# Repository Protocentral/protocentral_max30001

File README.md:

# ProtoCentral MAX30001 ECG and Respiration/Bio-Impedance Breakout Board

If you dont already have one, you can buy [ProtoCentral MAX30001 ECG and Respiration/Bio-Impedance Breakout Board here.](https://protocentral.com/product/protocentral-max30001/)

MAX30001 is a single-lead ECG monitoring IC which has built-in R-R detection and several other features that make it perfect for a wearable single-lead ECG application.  

Several new features on this chip make it ideal for wearable applications. First is the low power consumption - just 85 uW of power and can work from 1.1 V onwards ! Also of interest is the fact that it can work with only two chest electrodes without the need for a third right-leg drive (DRL) electrode.

The best feature of this chip though is the built-in R-R detection algorithm which can measure the time between successive peaks of the QRS complex of the ECG. This means that heart-computation comes right out of the box without any microcontroller-side code requirement. Heart-rate computation just got a lot easier !!

# Features

* MAX30001 single channel integrated front-end (AFE) chip
* Single-lead ECG monitoring ( three electrodes, optional right leg drive)
* Capable of measuring respiration
* Clinical-Grade ECG and BioZ AFE with High Resolution
* Inbuilt R-R detection and Pace detection
* Flexibility for 2 or 3 electrode measurements
* ADC Resolution is 18 bits 
* High DC Offset range of ±650mV(excellent tolerance to motion artifacts)
* Onboard 3.3V voltage regulator for low noise.
* Onboard logic level translators for Arduino interface.

# What's included

* ProtoCentral MAX30001 ECG and Respiration/Bio-Impedance Breakout Board
* Straight pin headers
* 2-electrode ECG connector with stereo connector
* 10x disposable ECG stick-on electrodes

# Repository Contents

* **/software** - Arduino library and example sketches.
* **/hardware** - All Eagle hardware design files

# Wiring the board to your Arduino

If you have bought the breakout the connection with the Arduino board is as follows:

|MAX30001 pin label| Arduino Connection   |Pin Function      |
|----------------- |:--------------------:|-----------------:|
| MISO             | D12                  |  Slave out|             
| MOSI             | D11                  |  Slave in           |
| SCK              | D13                  |  Serial clock     |
| CS0              | D7                   |  Slave select|
| FCLK             | NC                   |  External clock(32KHz)     |
| INT1             | D2                   |  Interrupt        |
| INT2             | NC                   |  Interrupt       |
| 3V3              | Supply               |  Board which supports 3.3V and 1.8V    |
| VCC              | Supply 5V            | 5V            |
| GND              | Gnd  

# Running the Arduino Sketch

If you have correctly installed the libraries, the example sketeches should now be available from within Arduino.

[Download the Arduino Sketch here for this board here.](https://github.com/Protocentral/protocentral_max30001/releases/download/v0.1/protocentral_max30001_arduino.zip)

Open up your Arduino IDE and run the Arudino sketch (.ino) file in the archive that you downloaded. Your Arduino should now be programmed to read the ecg data and sending over the USB-UART.  

# Using the ProtoCentral OpenView GUI

The GUI for visualizing the ECG and Respiration as well as parameters like Heart rate and Respiration rate is written in Processing, based on Java and is cross-compilable across platforms.

Java 8 is required on all platforms for running the processing-based GUI application. You can download Java for your platform from the [Official Java website](https://www.java.com/en/download/).

You can download and install [ProtoCentral OpenView from here](https://github.com/Protocentral/protocentral_openview).

Once you have opened OpenView, make sure to select "MAX30001 breakout" under the "Board" dropdown. 

# Connecting the ECG Electrodes

A 2-electrode cable along with a standard stereo jack is provided along with the shield to connect the electrodes to the board. The electrode input connector is highlighted in the below picture.

The other side of the electrode connector would connect to snap-on electrodes attached to the body. For testing purposes, you can use an ECG simulator to provide inputs to the board.

*Warning:
When connecting the electodes to the body, it is safer to disconnect the mains power source to the Arduino. For example, if  you are using the Arduino along with a laptop, disconnecting the battery charger from the laptop would be a safe option.*

# Placing the Electrodes on the body

License Information
===================

This product is open source! Both, our hardware and software are open source and licensed under the following licenses:

Hardware
---------

**All hardware is released under the [CERN-OHL-P v2](https://ohwr.org/cern_ohl_p_v2.txt)** license.

Copyright CERN 2020.

This source describes Open Hardware and is licensed under the CERN-OHL-P v2.

You may redistribute and modify this documentation and make products
using it under the terms of the CERN-OHL-P v2 (https:/cern.ch/cern-ohl).
This documentation is distributed WITHOUT ANY EXPRESS OR IMPLIED
WARRANTY, INCLUDING OF MERCHANTABILITY, SATISFACTORY QUALITY
AND FITNESS FOR A PARTICULAR PURPOSE. Please see the CERN-OHL-P v2
for applicable conditions

Software
--------

**All software is released under the MIT License(http://opensource.org/licenses/MIT).**

THE SOFTWARE IS PROVIDED "AS IS", WITHOUT WARRANTY OF ANY KIND, EXPRESS OR IMPLIED, INCLUDING BUT NOT LIMITED TO THE WARRANTIES OF MERCHANTABILITY, FITNESS FOR A PARTICULAR PURPOSE AND NONINFRINGEMENT. IN NO EVENT SHALL THE AUTHORS OR COPYRIGHT HOLDERS BE LIABLE FOR ANY CLAIM, DAMAGES OR OTHER LIABILITY, WHETHER IN AN ACTION OF CONTRACT, TORT OR OTHERWISE, ARISING FROM, OUT OF OR IN CONNECTION WITH THE SOFTWARE OR THE USE OR OTHER DEALINGS IN THE SOFTWARE.

Documentation
-------------
**All documentation is released under [Creative Commons Share-alike 4.0 International](http://creativecommons.org/licenses/by-sa/4.0/).**

You are free to:

* Share — copy and redistribute the material in any medium or format
* Adapt — remix, transform, and build upon the material for any purpose, even commercially.
The licensor cannot revoke these freedoms as long as you follow the license terms.

Under the following terms:

* Attribution — You must give appropriate credit, provide a link to the license, and indicate if changes were made. You may do so in any reasonable manner, but not in any way that suggests the licensor endorses you or your use.
* ShareAlike — If you remix, transform, or build upon the material, you must distribute your contributions under the same license as the original.

Please check [*LICENSE.md*](LICENSE.md) for detailed license descriptions.

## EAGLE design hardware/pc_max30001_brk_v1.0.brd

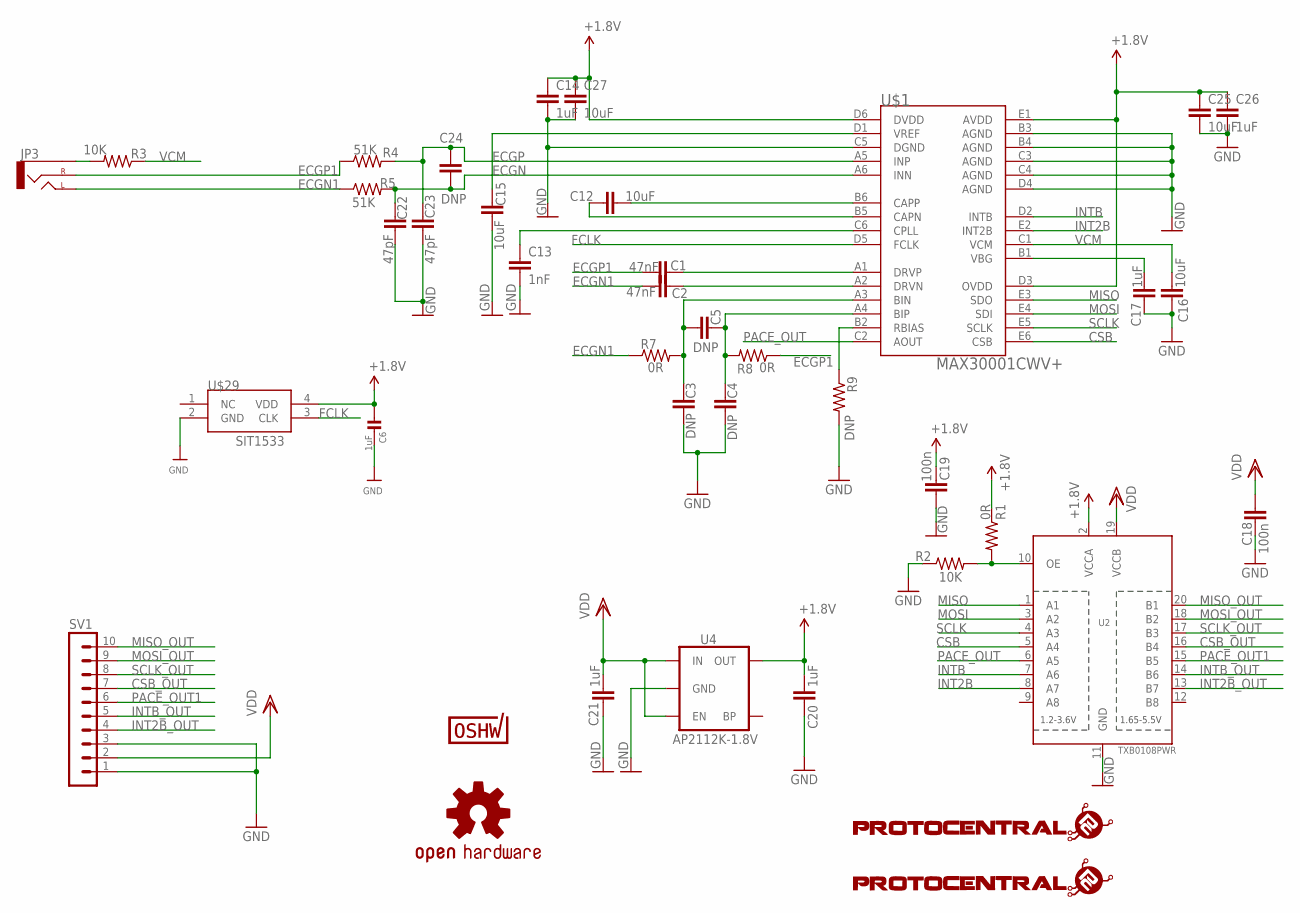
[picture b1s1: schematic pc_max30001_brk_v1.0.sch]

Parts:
C1, C2: 47nF; C0402
C3, C4, C5, C24: DNP; C0402
C6: 1uF; 0402
C12, C15, C16, C25, C27: 10uF; C0805
C13: 1nF; C0402
C14, C17, C26: 1uF; C0402
C18, C19: 100n; C0402
C20, C21: 1uF; C0805
C22, C23: 47pF; C0402
JP3: AUDIO-JACKSMD2; AUDIO-JACK-3.5MM-SMD
R1: 0R; 0805
R2, R3: 10K; 0805
R4, R5: 51K; 0805
R7, R8: 0R; 0402-RES
R9: DNP; 0402-RES
SV1: MA10-1
U2: TXB0108PWR; TSSOP20
U4: AP2112K-1.8V; SOT23-5
U$1: MAX30001CWV+; 30WLP
U$3: PROTY-LOGO; LOGO-PROTY
U$4: PROTY_LOGO_WITH_TEXT; PROTY_WITH_TEXT
U$6: OSHW-LOGOS; OSHW-LOGO-S
U$7: CERT-SMALL; CERT-SMALL-SILK
U$29: SIT1533

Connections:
+1.8V: C6.1, C14.1, C19.2, C20.2, C25.1, C26.1, C27.1, R1.1, U2.2 (VCCA), U4.5 (OUT), U$1.D3 (OVDD), U$1.D6 (DVDD), U$1.E1 (AVDD), U$29.4 (VDD)
CSB: U2.5 (A4), U$1.E6 (CSB)
CSB_OUT: SV1.7, U2.16 (B4)
ECGN: C22.1, C24.2, R5.2, U$1.A6 (INN)
ECGN1: C2.1, JP3.TIP (LEFT), R5.1, R7.1
ECGP: C23.1, C24.1, R4.2, U$1.A5 (INP)
ECGP1: C1.1, JP3.RING (RIGHT), R4.1, R8.1
FCLK: U$1.D5 (FCLK), U$29.3 (CLK)
GND: C3.2, C4.2, C6.2, C13.2, C14.2, C15.2, C16.2, C17.2, C18.1, C19.1, C20.1, C21.1, C22.2, C23.2, C25.2, C26.2, C27.2, R2.1, R9.2, SV1.1, SV1.3, U2.11 (GND), U4.2 (GND), U$1.B3 (AGND), U$1.B4 (AGND), U$1.C3 (AGND), U$1.C4 (AGND), U$1.C5 (DGND), U$1.D4 (AGND), U$29.2 (GND)
INT2B: U2.8 (A7), U$1.E2 (INT2B)
INT2B_OUT: SV1.4, U2.13 (B7)
INTB: U2.7 (A6), U$1.D2 (INTB)
INTB_OUT: SV1.5, U2.14 (B6)
MISO: U2.1 (A1), U$1.E3 (SDO)
MISO_OUT: SV1.10, U2.20 (B1)
MOSI: U2.3 (A2), U$1.E4 (SDI)
MOSI_OUT: SV1.9, U2.18 (B2)
unnamed: C12.1, U$1.B6 (CAPP)
unnamed: C1.2, U$1.A1 (DRVP)
unnamed: C2.2, U$1.A2 (DRVN)
unnamed: C3.1, C5.1, R7.2, U$1.A3 (BIN)
unnamed: C4.1, C5.2, R8.2, U$1.A4 (BIP)
unnamed: R9.1, U$1.B2 (RBIAS)
unnamed: C13.1, U$1.C6 (CPLL)
unnamed: C12.2, U$1.B5 (CAPN)
unnamed: C15.1, U$1.D1 (VREF)
unnamed: C17.1, U$1.B1 (VBG)
unnamed: R1.2, R2.2, U2.10 (OE)
unnamed: JP3.SLEEVE, R3.2
PACE_OUT: U2.6 (A5), U$1.C2 (AOUT)
PACE_OUT1: SV1.6, U2.15 (B5)
SCLK: U2.4 (A3), U$1.E5 (SCLK)
SCLK_OUT: SV1.8, U2.17 (B3)
VCM: C16.1, R3.1, U$1.C1 (VCM)
VDD: C18.2, C21.2, SV1.2, U2.19 (VCCB), U4.1 (IN), U4.3 (EN)

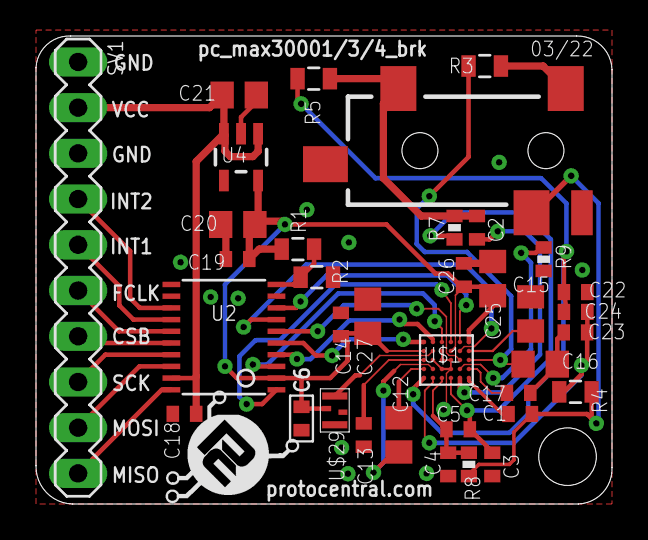
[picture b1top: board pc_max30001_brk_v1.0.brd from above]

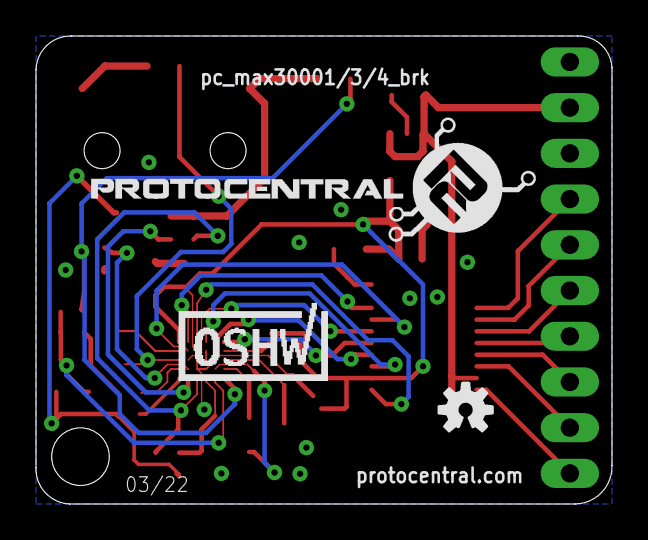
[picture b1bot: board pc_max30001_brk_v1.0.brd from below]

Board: 4 copper layers, 32.0 x 26.0 mm, 40 parts (3 on the bottom side), 35 nets.

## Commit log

2022-04-24 Added New example for BioZ
2022-04-26 Enabled BioZ channel. Resp not working
2022-06-25 Corrected example 2
2022-09-26 ECG & Respiration now working
2022-09-26 Corrected packet format in example
2022-09-27 Updated examples
2022-09-27 Library optimization
2022-10-07 Changed default settings for BioZ
2022-10-07 Updated example code
2022-10-08 Added banner
2022-10-08 Removed Arduino Library files

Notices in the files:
README.md:
CC-BY-SA-4.0
parts and their libraries:
SparkFun-PowerIC: Licensing: Creative Commons ShareAlike 4.0 International - https://creativecommons.org/licenses/by-sa/4.0
microbuilder: This work is placed in the public domain, and may be freely used for commercial and non-commercial work with the following conditions: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
